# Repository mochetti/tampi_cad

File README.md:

# Tampi CAD

Arquivos do Eagle e AutoCAD para o Tampi

## Contribuição

Todas as sugestões são bem vindas. Caso encontre um bug, fique à vontade para [abrir uma issue](https://github.com/mochetti/tampi_cad/issues/new).

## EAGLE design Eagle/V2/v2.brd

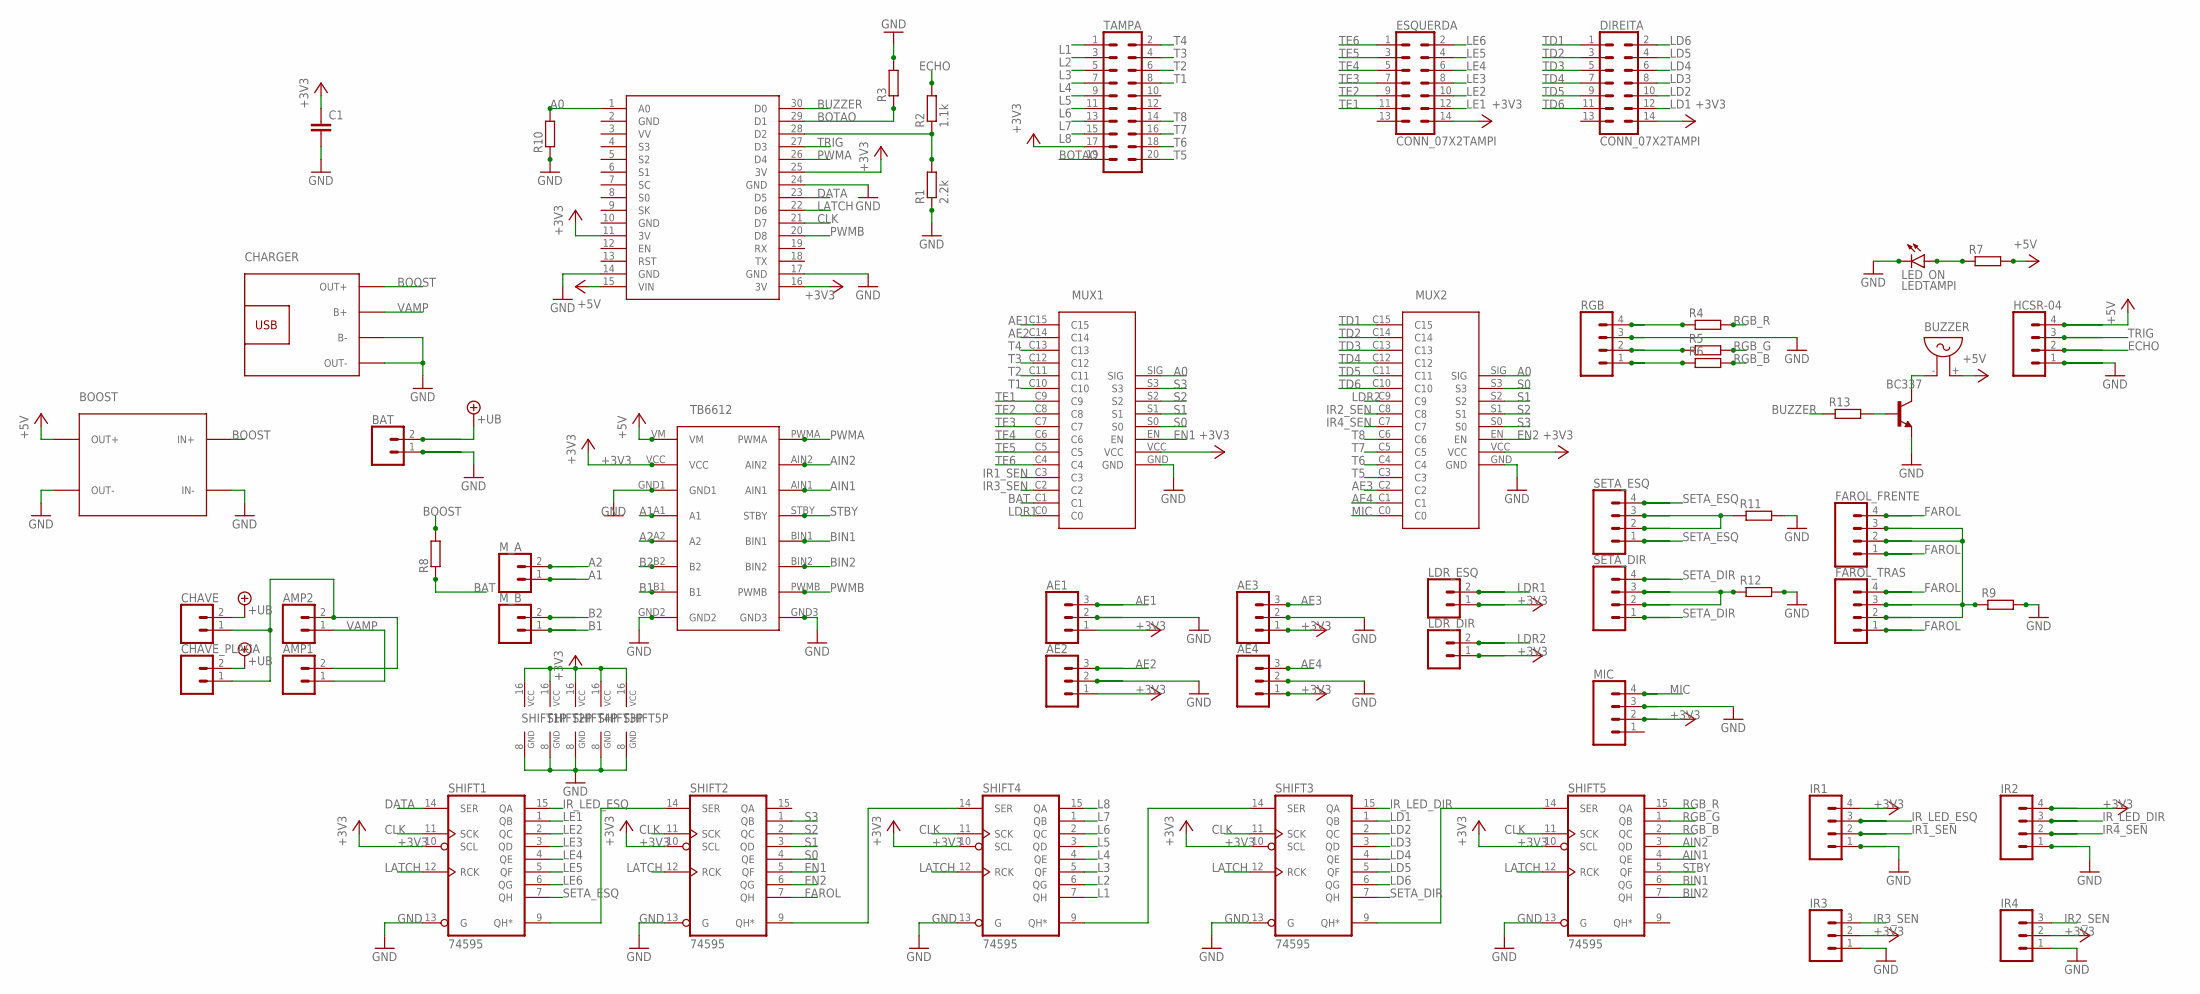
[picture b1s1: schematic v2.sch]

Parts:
AE1, AE2, AE3, AE4: CONN_03TAMPI; TAMPI_1X03
AMP1, AMP2: CONN_02TAMPI; TAMPI_1X02
BAT: CONN_02TAMPI; TAMPI_1X02
BC337: BC337; TAMPI_BC337
BOOST: MT3608TAMPI; TAMPI_MT3608
BUZZER: BUZZERTAMPI; TAMPI_BUZZER
C1: CAPACITORTAMPI; TAMPI_C2.5-3
CHARGER: TP4056TAMPI; TAMPI_TP4056
CHAVE: CONN_02TAMPI; TAMPI_1X02
CHAVE_PLACA: CONN_02TAMPI; TAMPI_1X02
DIREITA: CONN_07X2TAMPI; TAMPI_2X7
ESQUERDA: CONN_07X2TAMPI; TAMPI_2X7
FAROL_FRENTE: CONN_04; TAMPI_1X04
FAROL_TRAS: CONN_04; TAMPI_1X04
HCSR-04: CONN_04; TAMPI_1X04
IR1, IR2: CONN_04; TAMPI_1X04
IR3, IR4: CONN_03TAMPI; TAMPI_1X03
LDR_DIR: CONN_02TAMPI; TAMPI_1X02
LDR_ESQ: CONN_02TAMPI; TAMPI_1X02
LED_ON: LEDTAMPI; TAMPI_LED3MM
MIC: CONN_04; TAMPI_1X04
MUX1, MUX2: 4067TAMPI; TAMPI_4067
M_A: CONN_02TAMPI; TAMPI_1X02
M_B: CONN_02TAMPI; TAMPI_1X02
R1: 2.2k; TAMPI_RES
R2: 1.1k; TAMPI_RES
R3, R4, R5, R6, R7, R8, R9, R10, R11, R12, R13: RESISTOR; TAMPI_RES
RGB: CONN_04; TAMPI_1X04
SETA_DIR: CONN_04; TAMPI_1X04
SETA_ESQ: CONN_04; TAMPI_1X04
SHIFT1, SHIFT2, SHIFT3, SHIFT4, SHIFT5: 74595; TAMPI_74595
TAMPA: CONN_10X2TAMPI; TAMPI_2X10
TB6612: TB6612FNGTAMPI; TAMPI_TB6612
U$1: NODEMCUTAMPI; TAMPI_NODEMCU

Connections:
+3V3: AE1.1, AE2.1, AE3.1, AE4.1, C1.1, DIREITA.14, ESQUERDA.14, IR1.4, IR2.4, IR3.2, IR4.2, LDR_DIR.1, LDR_ESQ.1, MIC.2, MUX1.VCC, MUX2.VCC, SHIFT1.10 (SCL), SHIFT1.16 (VCC), SHIFT2.10 (SCL), SHIFT2.16 (VCC), SHIFT3.10 (SCL), SHIFT3.16 (VCC), SHIFT4.10 (SCL), SHIFT4.16 (VCC), SHIFT5.10 (SCL), SHIFT5.16 (VCC), TAMPA.17, TB6612.VCC, U$1.11 (3V), U$1.16 (3V), U$1.25 (3V)
+5V: BOOST.OUT+, BUZZER.+ (2), HCSR-04.4, R7.2, TB6612.VM, U$1.15 (VIN)
+UB: BAT.2, CHAVE.2, CHAVE_PLACA.2
A0: MUX1.SIG, MUX2.SIG, R10.2, U$1.1 (A0)
A1: M_A.1, TB6612.A1
A2: M_A.2, TB6612.A2
AE1: AE1.3, MUX1.C15
AE2: AE2.3, MUX1.C14
AE3: AE3.3, MUX2.C2
AE4: AE4.3, MUX2.C1
AIN1: SHIFT5.4 (QE), TB6612.AIN1
AIN2: SHIFT5.3 (QD), TB6612.AIN2
B1: M_B.1, TB6612.B1
B2: M_B.2, TB6612.B2
BAT: MUX1.C1, R8.1
BIN1: SHIFT5.6 (QG), TB6612.BIN1
BIN2: SHIFT5.7 (QH), TB6612.BIN2
BOOST: BOOST.IN+, CHARGER.OUT+, R8.2
BOTAO: R3.1, TAMPA.19, U$1.29 (D1)
BUZZER: R13.1, U$1.30 (D0)
CLK: SHIFT1.11 (SCK), SHIFT2.11 (SCK), SHIFT3.11 (SCK), SHIFT4.11 (SCK), SHIFT5.11 (SCK), U$1.21 (D7)
DATA: SHIFT1.14 (SER), U$1.23 (D5)
ECHO: HCSR-04.2, R2.2
EN1: MUX1.EN, SHIFT2.5 (QF)
EN2: MUX2.EN, SHIFT2.6 (QG)
FAROL: FAROL_FRENTE.1, FAROL_FRENTE.4, FAROL_TRAS.1, FAROL_TRAS.4, SHIFT2.7 (QH)
GND: AE1.2, AE2.2, AE3.2, AE4.2, BAT.1, BC337.1 (E), BOOST.IN-, BOOST.OUT-, C1.2, CHARGER.B-, CHARGER.OUT-, HCSR-04.1, IR1.1, IR2.1, IR3.1, IR4.1, LED_ON.K (C), MIC.3, MUX1.GND, MUX2.GND, R1.1, R3.2, R9.2, R10.1, R11.2, R12.2, RGB.3, SHIFT1.8 (GND), SHIFT1.13 (G), SHIFT2.8 (GND), SHIFT2.13 (G), SHIFT3.8 (GND), SHIFT3.13 (G), SHIFT4.8 (GND), SHIFT4.13 (G), SHIFT5.8 (GND), SHIFT5.13 (G), TB6612.GND1, TB6612.GND2, TB6612.GND3, U$1.2 (GND), U$1.10 (GND), U$1.14 (GND), U$1.17 (GND), U$1.24 (GND)
IR1_SEN: IR1.2, MUX1.C3
IR2_SEN: IR4.3, MUX2.C8
IR3_SEN: IR3.3, MUX1.C2
IR4_SEN: IR2.2, MUX2.C7
IR_LED_DIR: IR2.3, SHIFT3.15 (QA)
IR_LED_ESQ: IR1.3, SHIFT1.15 (QA)
L1: SHIFT4.7 (QH), TAMPA.1
L2: SHIFT4.6 (QG), TAMPA.3
L3: SHIFT4.5 (QF), TAMPA.5
L4: SHIFT4.4 (QE), TAMPA.7
L5: SHIFT4.3 (QD), TAMPA.9
L6: SHIFT4.2 (QC), TAMPA.11
L7: SHIFT4.1 (QB), TAMPA.13
L8: SHIFT4.15 (QA), TAMPA.15
LATCH: SHIFT1.12 (RCK), SHIFT2.12 (RCK), SHIFT3.12 (RCK), SHIFT4.12 (RCK), SHIFT5.12 (RCK), U$1.22 (D6)
LD1: DIREITA.12, SHIFT3.1 (QB)
LD2: DIREITA.10, SHIFT3.2 (QC)
LD3: DIREITA.8, SHIFT3.3 (QD)
LD4: DIREITA.6, SHIFT3.4 (QE)
LD5: DIREITA.4, SHIFT3.5 (QF)
LD6: DIREITA.2, SHIFT3.6 (QG)
LDR1: LDR_ESQ.2, MUX1.C0
LDR2: LDR_DIR.2, MUX2.C9
LE1: ESQUERDA.12, SHIFT1.1 (QB)
LE2: ESQUERDA.10, SHIFT1.2 (QC)
LE3: ESQUERDA.8, SHIFT1.3 (QD)
LE4: ESQUERDA.6, SHIFT1.4 (QE)
LE5: ESQUERDA.4, SHIFT1.5 (QF)
LE6: ESQUERDA.2, SHIFT1.6 (QG)
MIC: MIC.4, MUX2.C0
unnamed: R4.1, RGB.4
unnamed: R5.1, RGB.2
unnamed: R6.1, RGB.1
unnamed: R11.1, SETA_ESQ.2, SETA_ESQ.3
unnamed: SHIFT1.9 (QH*), SHIFT2.14 (SER)
unnamed: FAROL_FRENTE.2, FAROL_FRENTE.3, FAROL_TRAS.2, FAROL_TRAS.3, R9.1
unnamed: R12.1, SETA_DIR.2, SETA_DIR.3
unnamed: AMP1.2, AMP2.2, CHAVE.1, CHAVE_PLACA.1
unnamed: BC337.2 (B), R13.2
unnamed: BC337.3 (C), BUZZER.- (1)
unnamed: LED_ON.A, R7.1
unnamed: SHIFT3.9 (QH*), SHIFT5.14 (SER)
unnamed: SHIFT3.14 (SER), SHIFT4.9 (QH*)
unnamed: SHIFT2.9 (QH*), SHIFT4.14 (SER)
unnamed: R1.2, R2.1, U$1.28 (D2)
PWMA: TB6612.PWMA, U$1.26 (D4)
PWMB: TB6612.PWMB, U$1.20 (D8)
RGB_B: R6.2, SHIFT5.2 (QC)
RGB_G: R5.2, SHIFT5.1 (QB)
RGB_R: R4.2, SHIFT5.15 (QA)
S0: MUX1.S0, MUX2.S3, SHIFT2.4 (QE)
S1: MUX1.S1, MUX2.S2, SHIFT2.3 (QD)
S2: MUX1.S2, MUX2.S1, SHIFT2.2 (QC)
S3: MUX1.S3, MUX2.S0, SHIFT2.1 (QB)
SETA_DIR: SETA_DIR.1, SETA_DIR.4, SHIFT3.7 (QH)
SETA_ESQ: SETA_ESQ.1, SETA_ESQ.4, SHIFT1.7 (QH)
STBY: SHIFT5.5 (QF), TB6612.STBY
T1: MUX1.C10, TAMPA.8
T2: MUX1.C11, TAMPA.6
T3: MUX1.C12, TAMPA.4
T4: MUX1.C13, TAMPA.2
T5: MUX2.C3, TAMPA.20
T6: MUX2.C4, TAMPA.18
T7: MUX2.C5, TAMPA.16
T8: MUX2.C6, TAMPA.14
TD1: DIREITA.1, MUX2.C15
TD2: DIREITA.3, MUX2.C14
TD3: DIREITA.5, MUX2.C13
TD4: DIREITA.7, MUX2.C12
TD5: DIREITA.9, MUX2.C11
TD6: DIREITA.11, MUX2.C10
TE1: ESQUERDA.11, MUX1.C9
TE2: ESQUERDA.9, MUX1.C8
TE3: ESQUERDA.7, MUX1.C7
TE4: ESQUERDA.5, MUX1.C6
TE5: ESQUERDA.3, MUX1.C5
TE6: ESQUERDA.1, MUX1.C4
TRIG: HCSR-04.3, U$1.27 (D3)
VAMP: AMP1.1, AMP2.1, CHARGER.B+

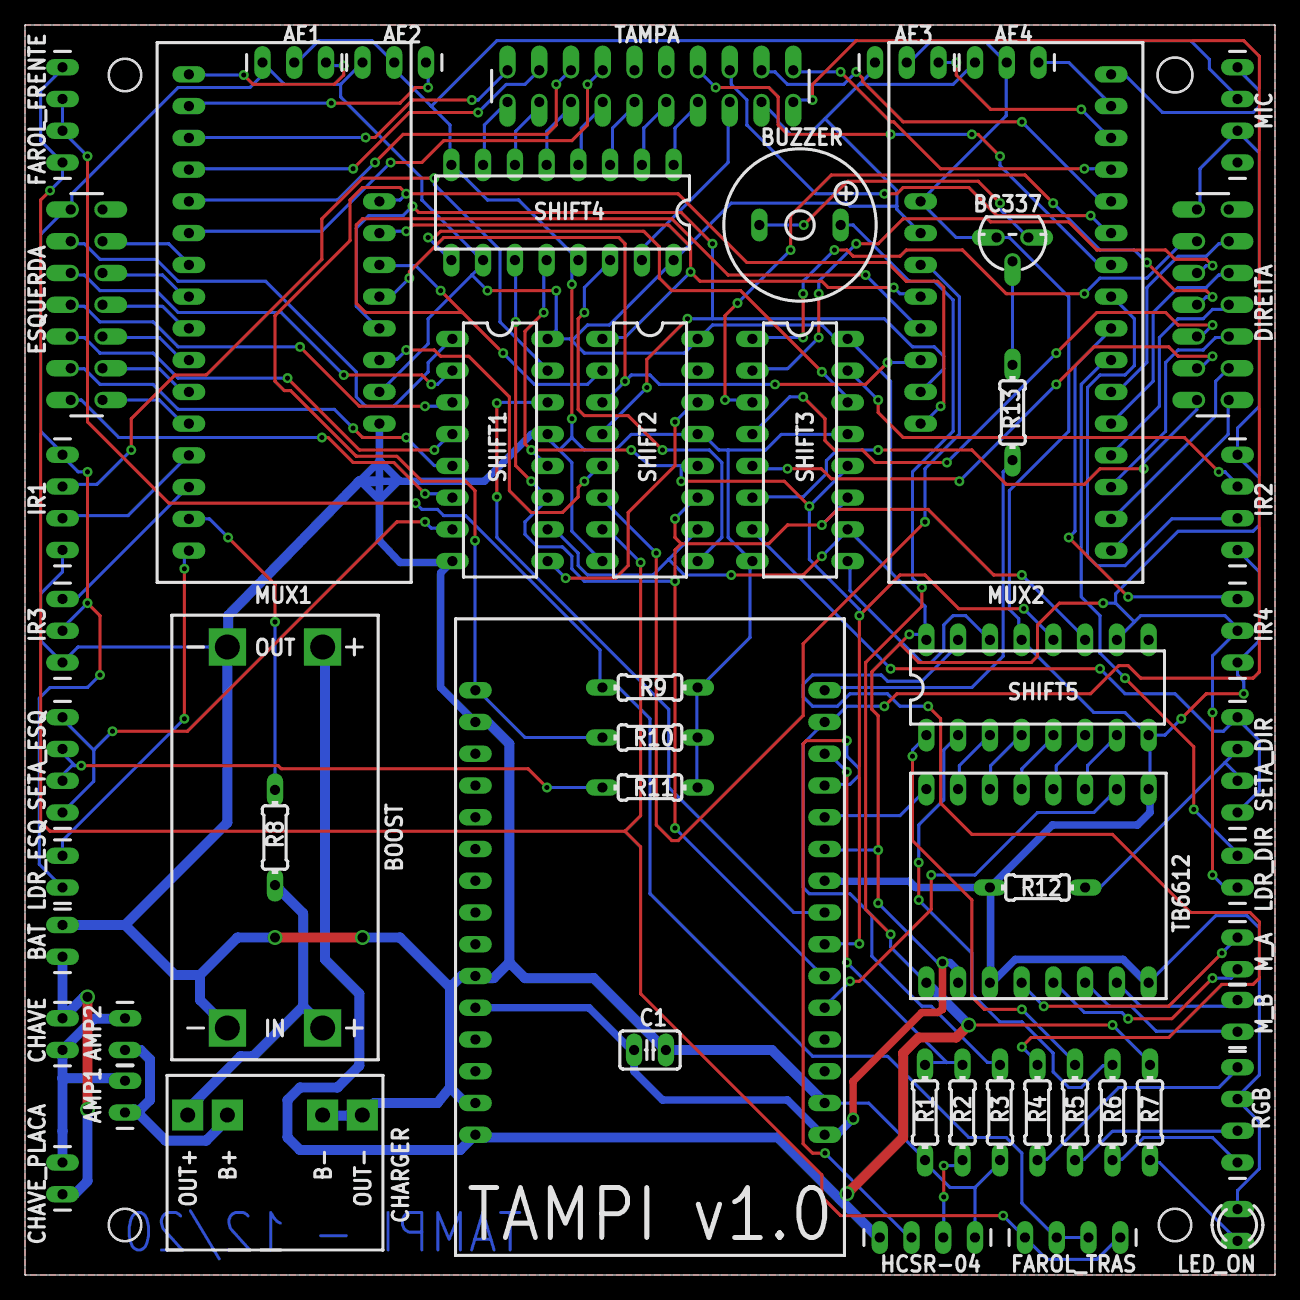
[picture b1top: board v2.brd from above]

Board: 2 copper layers, 100.0 x 100.0 mm, 55 parts (0 on the bottom side), 106 nets.

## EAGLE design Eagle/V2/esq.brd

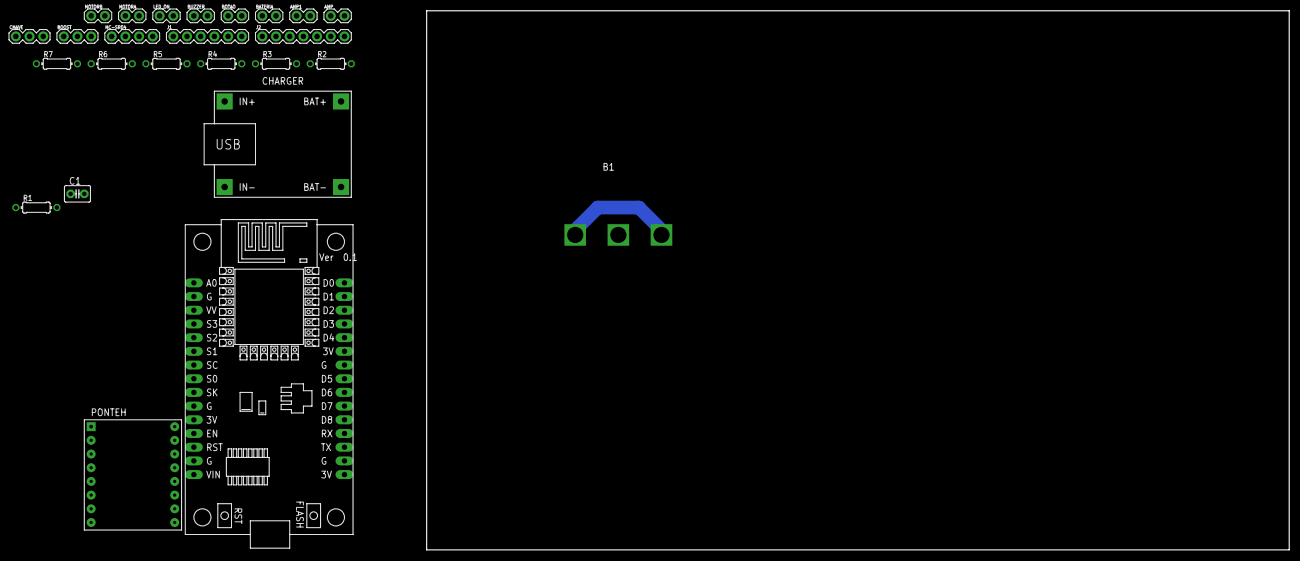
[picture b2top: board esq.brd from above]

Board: 2 copper layers, 160.0 x 100.0 mm, 25 parts (0 on the bottom side), 30 nets.

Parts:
AMP, AMP1: 1X02
B1: BOCAL
BATERIA: 1X02
BOOST: 1X03
BOTAO: 1X02
BUZZER: 1X02
C1: 10u; C2.5-3
CHARGER: BATTERY-CHARGER-LI-5V
CHAVE: 1X03
HC-SR04: 1X04
J1: 1X06
J2: 1X07
LED_ON: 1X02
MOTORA: 1X02
MOTORB: 1X02
NODEMCU: NODEMCU
PONTEH: TB6612FNG
R1: 4.7K; 0204/7
R2: 1.1K; 0204/7
R3: 2.2K; 0204/7
R4, R5: 10K; 0204/7
R6, R7: 100K; 0204/7

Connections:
+3V3: BOTAO.1, C1.1, J2.5, NODEMCU.11, NODEMCU.16, NODEMCU.25, PONTEH.VCC
+5V: BOOST.3, HC-SR04.4, NODEMCU.15, PONTEH.VM, R5.2
+UB: AMP.2, AMP1.1, BATERIA.2
A0: J2.6, NODEMCU.1, R1.2
AIN1: J1.4, PONTEH.AIN1
AIN2: J1.5, PONTEH.AIN2
BAT: J2.4, R6.1, R7.2
BIN1: J1.2, PONTEH.BIN1
BIN2: J1.1, PONTEH.BIN2
BOOST: BOOST.1, CHAVE.3, R6.2
BOTAO: BOTAO.2, J2.7, NODEMCU.29, R4.1
BUZZER: BUZZER.2, NODEMCU.30
CHARGER: CHARGER.BAT+, CHAVE.1
CLK: J2.1, NODEMCU.21
DATA: J2.3, NODEMCU.23
ECHO: HC-SR04.2, R2.2
GND: BATERIA.1, BOOST.2, BUZZER.1, C1.2, CHARGER.BAT-, HC-SR04.1, J1.6, LED_ON.1, NODEMCU.2, NODEMCU.10, NODEMCU.14, NODEMCU.17, NODEMCU.24, PONTEH.GND1, PONTEH.GND2, PONTEH.GND3, R1.1, R3.1, R4.2, R7.1
LATCH: J2.2, NODEMCU.22
unnamed: MOTORA.2, PONTEH.A1
unnamed: MOTORA.1, PONTEH.A2
unnamed: MOTORB.2, PONTEH.B2
unnamed: MOTORB.1, PONTEH.B1
unnamed: LED_ON.2, R5.1
unnamed: B1.P$1, B1.P$3
unnamed: NODEMCU.28, R2.1, R3.2
PWMA: NODEMCU.20, PONTEH.PWMA
PWMB: NODEMCU.26, PONTEH.PWMB
STBY: J1.3, PONTEH.STBY
TRIG: HC-SR04.3, NODEMCU.27
VAMP: AMP.1, AMP1.2, CHAVE.2

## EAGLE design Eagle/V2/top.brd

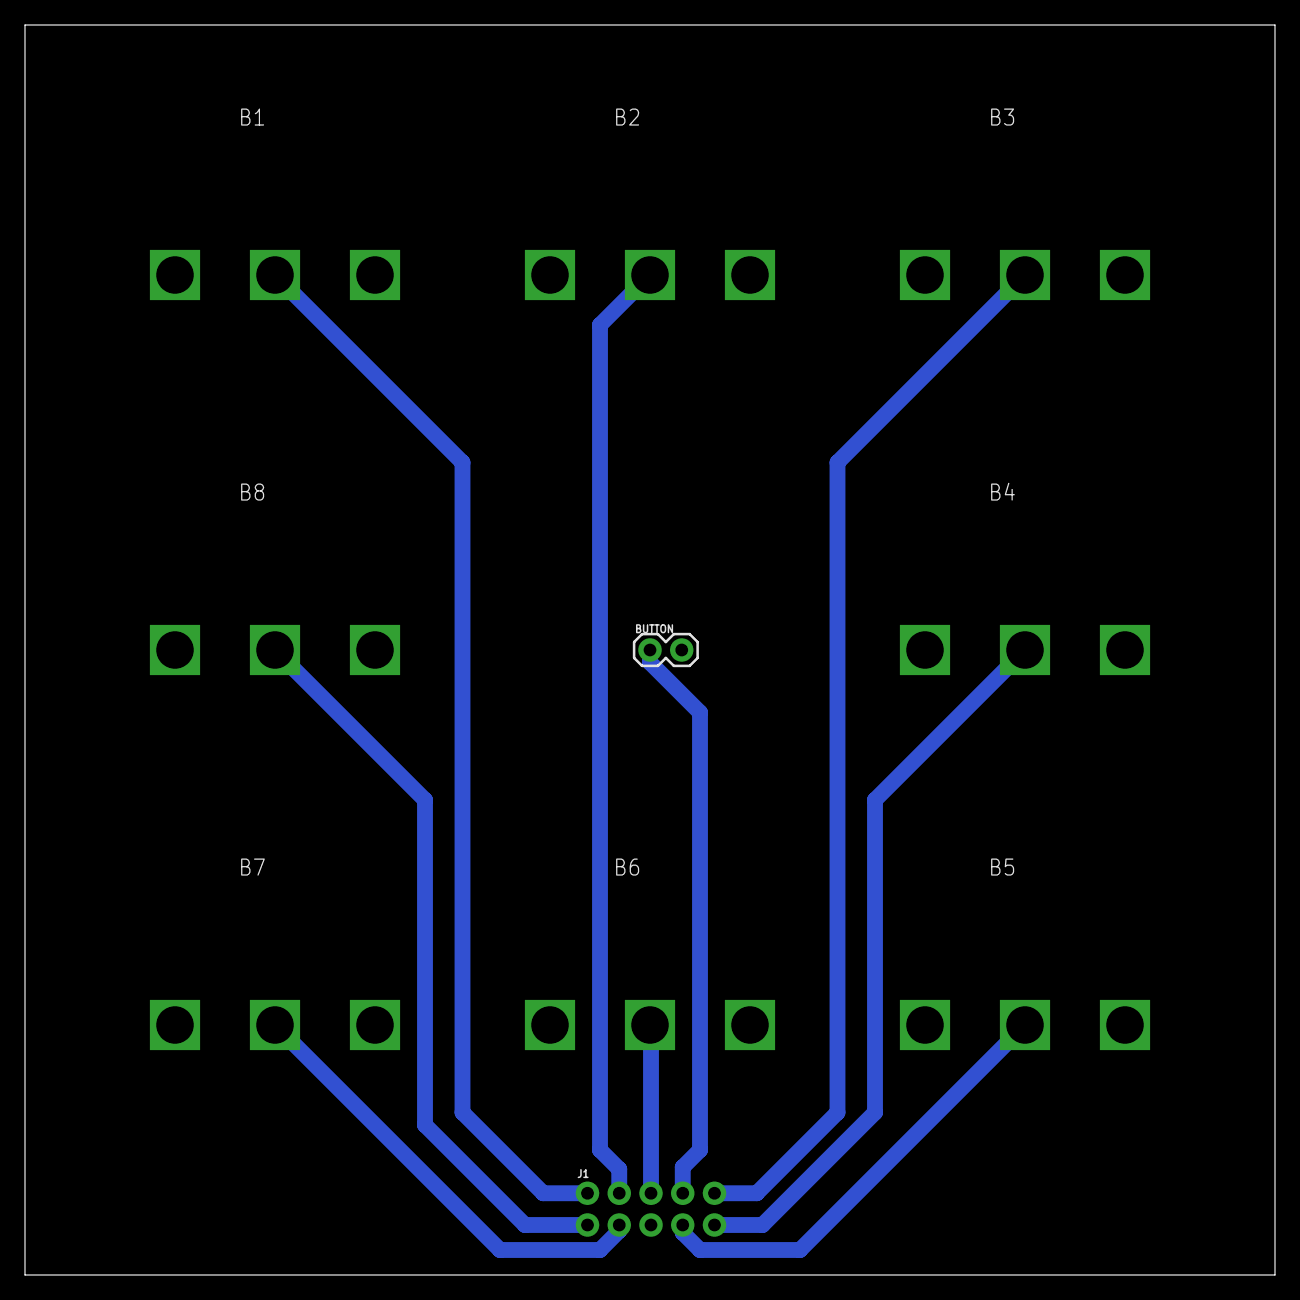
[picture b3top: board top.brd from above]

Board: 2 copper layers, 100.0 x 100.0 mm, 10 parts (0 on the bottom side), 10 nets.

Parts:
B1, B2, B3, B4, B5, B6, B7, B8: BOCAL
BUTTON: 1X02
J1: 2X5_NOSILK

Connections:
CB1: B1.P$2, J1.2
CB2: B2.P$2, J1.4
CB3: B3.P$2, J1.10
CB4: B4.P$2, J1.9
CB5: B5.P$2, J1.7
CB6: B6.P$2, J1.6
CB7: B7.P$2, J1.3
CB8: B8.P$2, J1.1
CBB: BUTTON.1, J1.8
VCC: B1.P$1, B1.P$3, B2.P$1, B2.P$3, B3.P$1, B3.P$3, B4.P$1, B4.P$3, B5.P$1, B5.P$3, B6.P$1, B6.P$3, B7.P$1, B7.P$3, B8.P$1, B8.P$3, BUTTON.2, J1.5

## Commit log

2020-12-09 V1 added
2020-12-16 v1.0 finalizada
2020-12-17 Versão com trilhas maiores
2020-12-30 gerber files
2021-01-16 logo v1
2021-04-26 tampi lib

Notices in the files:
parts and their libraries:
SparkFun-Connectors: Licensing: Creative Commons ShareAlike 4.0 International - https://creativecommons.org/licenses/by-sa/4.0
diy-modules: Released under the Creative Commons Attribution 4.0 International License: http://creativecommons.org/licenses/by/4.0
